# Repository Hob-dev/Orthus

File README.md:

# Orthus

An ergonomic split keyboard PCB with an integrated capacitive trackpad, Sharp Memory Display, and speaker. Designed around Kailh Choc low-profile switches and styled after Nothing.

## Overview

Orthus is a 6×5 ortholinear split — two mirrored halves, one with the alpha cluster (`QWERT`/`ASDFG`/`ZXCV`) and a number row (`1`–`5`), the other with the right-hand alphas, symbols, and a numpad row. Each half carries:

- 30 Kailh Choc keys (5 columns × 5 rows of alpha + outer modifier column + bottom-row arrow/macro circles)
- An integrated **OrthusTrackpad** capacitive sensor zone
- A **Sharp Memory Display** for live status (signal, battery, WPM, layer)
- Two side encoders / buttons next to the display
- A speaker grille

Both halves side-by-side:

Top-down view:

## Status

**Functionally complete** — finishing touches remain before fabrication (see "Known gaps" below).

## Folder layout

```
Orthus/
├── KiCad/              Main KiCad 7+ project — open Orthus.kicad_pro
│   ├── Orthus.kicad_pcb        Main board layout
│   ├── Orthus.kicad_sch        Top-level schematic (loads sub-sheets)
│   ├── Left.kicad_sch          Left-half hierarchical sheet
│   ├── Right.kicad_sch         Right-half hierarchical sheet
│   ├── LeftMatrix.kicad_sch    Switch matrix sub-sheet
│   ├── OLED.kicad_sch          Display sub-sheet
│   ├── led.kicad_sch / led_r.kicad_sch   LED sub-sheets
│   ├── font/                   Custom silkscreen font SVGs (digits 0–9)
│   └── backups/                Dated KiCad auto-backups
├── Renders/            Project renders, layout studies, and WIP photos
├── 3D/                 Mechanical models — case, keycaps, trackpad
│   ├── Orthus.step / .stl / .gltf / .bin     Full assembly
│   ├── OrthusSimple*.step                    Simplified assembly variants
│   ├── OrthusKeycap*.step                    Keycap variants (Alt, TLBR, TRBL)
│   ├── AltarCap v2/v3.step                   Sculpted altar-style keycaps
│   ├── OrthusTrackpad*.step                  Trackpad PCB models
│   └── TM040YDHG32.step                      LCD reference model
├── Fabrication/        Trackpad grill cutouts (.dxf / .svg, square + slotted)
├── JLCPCB/             Empty — gerbers for the main PCB not yet generated
└── Components/
    ├── OrthusTrackpad/    Capacitive trackpad PCB (self-contained KiCad project + gerbers)
    └── OrthusSharp/       Sharp Memory Display breakout (KiCad project + gerbers)
```

## Components

| Component | Purpose | Status |
|---|---|---|
| **OrthusTrackpad** | Custom mutual-capacitance trackpad PCB integrated into each half. Self-contained KiCad project with its own JLCPCB gerber output. | Complete |
| **OrthusSharp** | Sharp Memory Display breakout, derived from an open-source `sharp_memory_display` design and significantly modified. KiCad 5 originals preserved under `Components/OrthusSharp/Legacy/`. | Complete |
| **OrthusMouseWheel** | Scroll wheel module — *not included in this repo, still under `Custom/Ergomania/OrthusMouseWheel/`.* | Unfinished |

## Alternative Renders

| | |
|---|---|
|  |  |
|  |  |
|  |  |
|  |  |

Layout studies and design exploration:

## Known gaps

- **No gerbers / JLCPCB order files** for the main Orthus PCB. `JLCPCB/` is an empty placeholder — gerbers need to be generated before fabrication.
- **No BOM / pick-and-place files** for the main PCB.
- **No assembly documentation** — refer to the hierarchical schematics under `KiCad/`.
- **3D model paths in `Orthus.kicad_pcb`** still reference absolute paths under `E:/EverythingKB/Custom/Ergomania/OrthusChoc/...`. The 3D viewer works locally because of this; for an open-source release these should be repointed at `Orthus/3D/`.
- **3D model path in `OrthusSharp.kicad_pro`** uses `../../Custom/Ergomania/test/OrthusSharp.step` (relative to its old location).
- **OrthusSharp `fp-lib-table`** carries hardcoded macOS paths (`/Users/karnadi/...`) inherited from the upstream fork — regenerate or repoint to your local KiCad libraries on first open.

## Attribution

`Components/OrthusSharp/` is derived from an open-source Sharp Memory Display breakout (see `Components/OrthusSharp/LICENSE`). Heavily modified for integration with Orthus.

## License

Orthus is licensed under the [Creative Commons Attribution-NonCommercial 4.0 International License (CC BY-NC 4.0)](https://creativecommons.org/licenses/by-nc/4.0/).

`Components/OrthusSharp/` is third-party and retains its original license — see [`Components/OrthusSharp/LICENSE`](Components/OrthusSharp/LICENSE).

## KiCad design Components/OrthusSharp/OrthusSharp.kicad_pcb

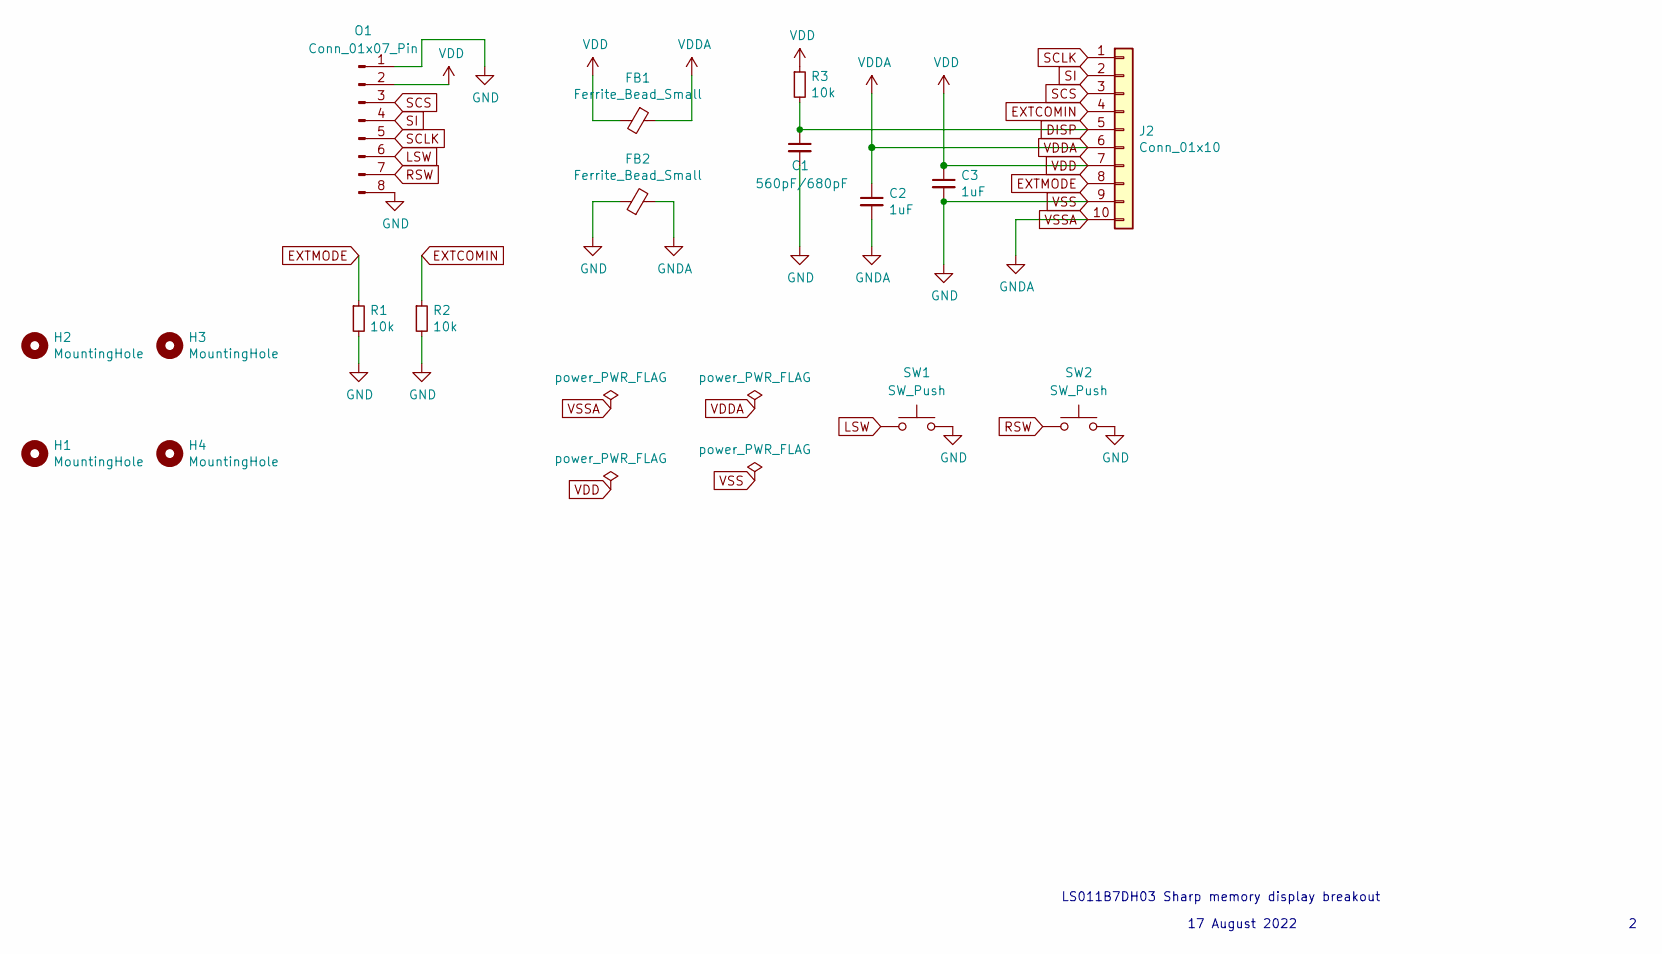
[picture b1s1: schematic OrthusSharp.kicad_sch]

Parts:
C1: 560pF/680pF; C_0603_1608Metric_Pad1.08x0.95mm_HandSolder; LCSC C84721
C2, C3: 1uF; C_0603_1608Metric_Pad1.08x0.95mm_HandSolder; LCSC C15849
FB1, FB2: Ferrite_Bead_Small; R_0805_2012Metric_Pad1.20x1.40mm_HandSolder; LCSC C1017
H1, H2, H3, H4: MountingHole; SMD-1_SMTSO1620MTJ
J2: Conn_01x10; FPC-SMD_10P-P0.50_XUNPU_FPC-05F-10PH15; LCSC C506791
O1: Conn_01x07_Pin; FPC-SMD_8P-P0.50_XUNPU_FPC-05F-8PH15
R1, R2, R3: 10k; R_0603_1608Metric_Pad0.98x0.95mm_HandSolder; LCSC C25804
SW1, SW2: SW_Push; SW-SMD_4P-L5.1-W5.1-P3.70-LS6.5-TL_H3.5

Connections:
DISP: C1.1, J2.5, R3.2
EXTCOMIN: J2.4, R2.1
EXTMODE: J2.8, R1.1
LSW: O1.6, SW1.1
RSW: O1.7, SW2.1
SCLK: J2.1, O1.5
SCS: J2.3, O1.3
SI: J2.2, O1.4
VDD: C3.1, FB1.2, J2.7, O1.2, R3.1
VDDA: C2.1, FB1.1, J2.6
VSS: C1.2, C3.2, FB2.1, J2.9, O1.1, O1.8, R1.2, R2.2, SW1.2, SW2.2
VSSA: C2.2, FB2.2, J2.10

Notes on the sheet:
17 August 2022
LS011B7DH03 Sharp memory display breakout

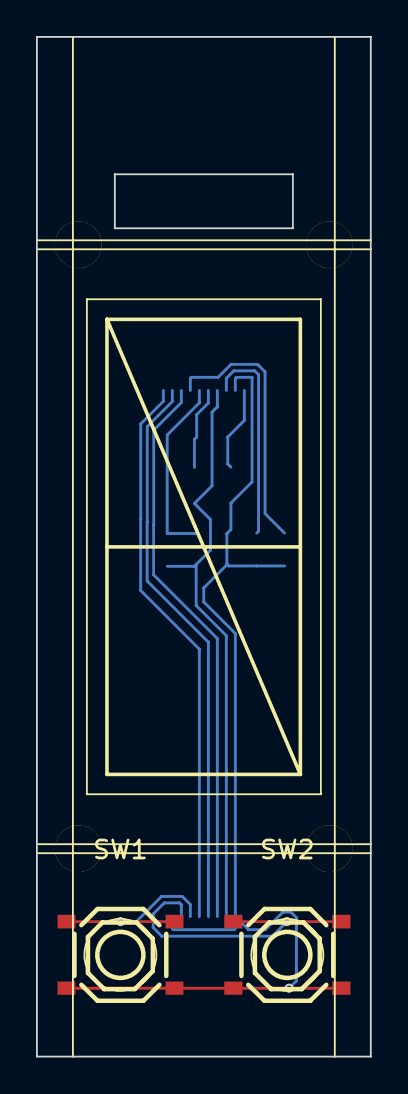
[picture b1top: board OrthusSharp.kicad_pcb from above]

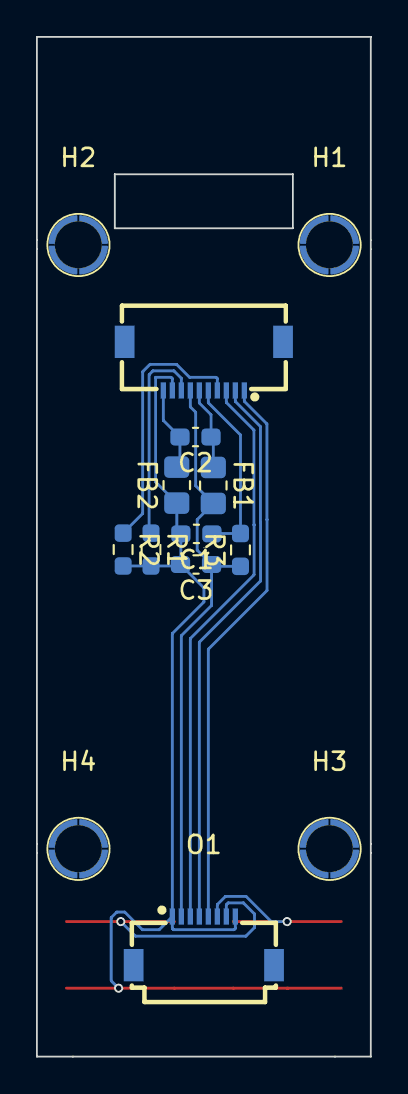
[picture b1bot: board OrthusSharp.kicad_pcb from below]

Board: 2 copper layers, 18.6 x 56.6 mm, 16 parts (14 on the bottom side), 12 nets.

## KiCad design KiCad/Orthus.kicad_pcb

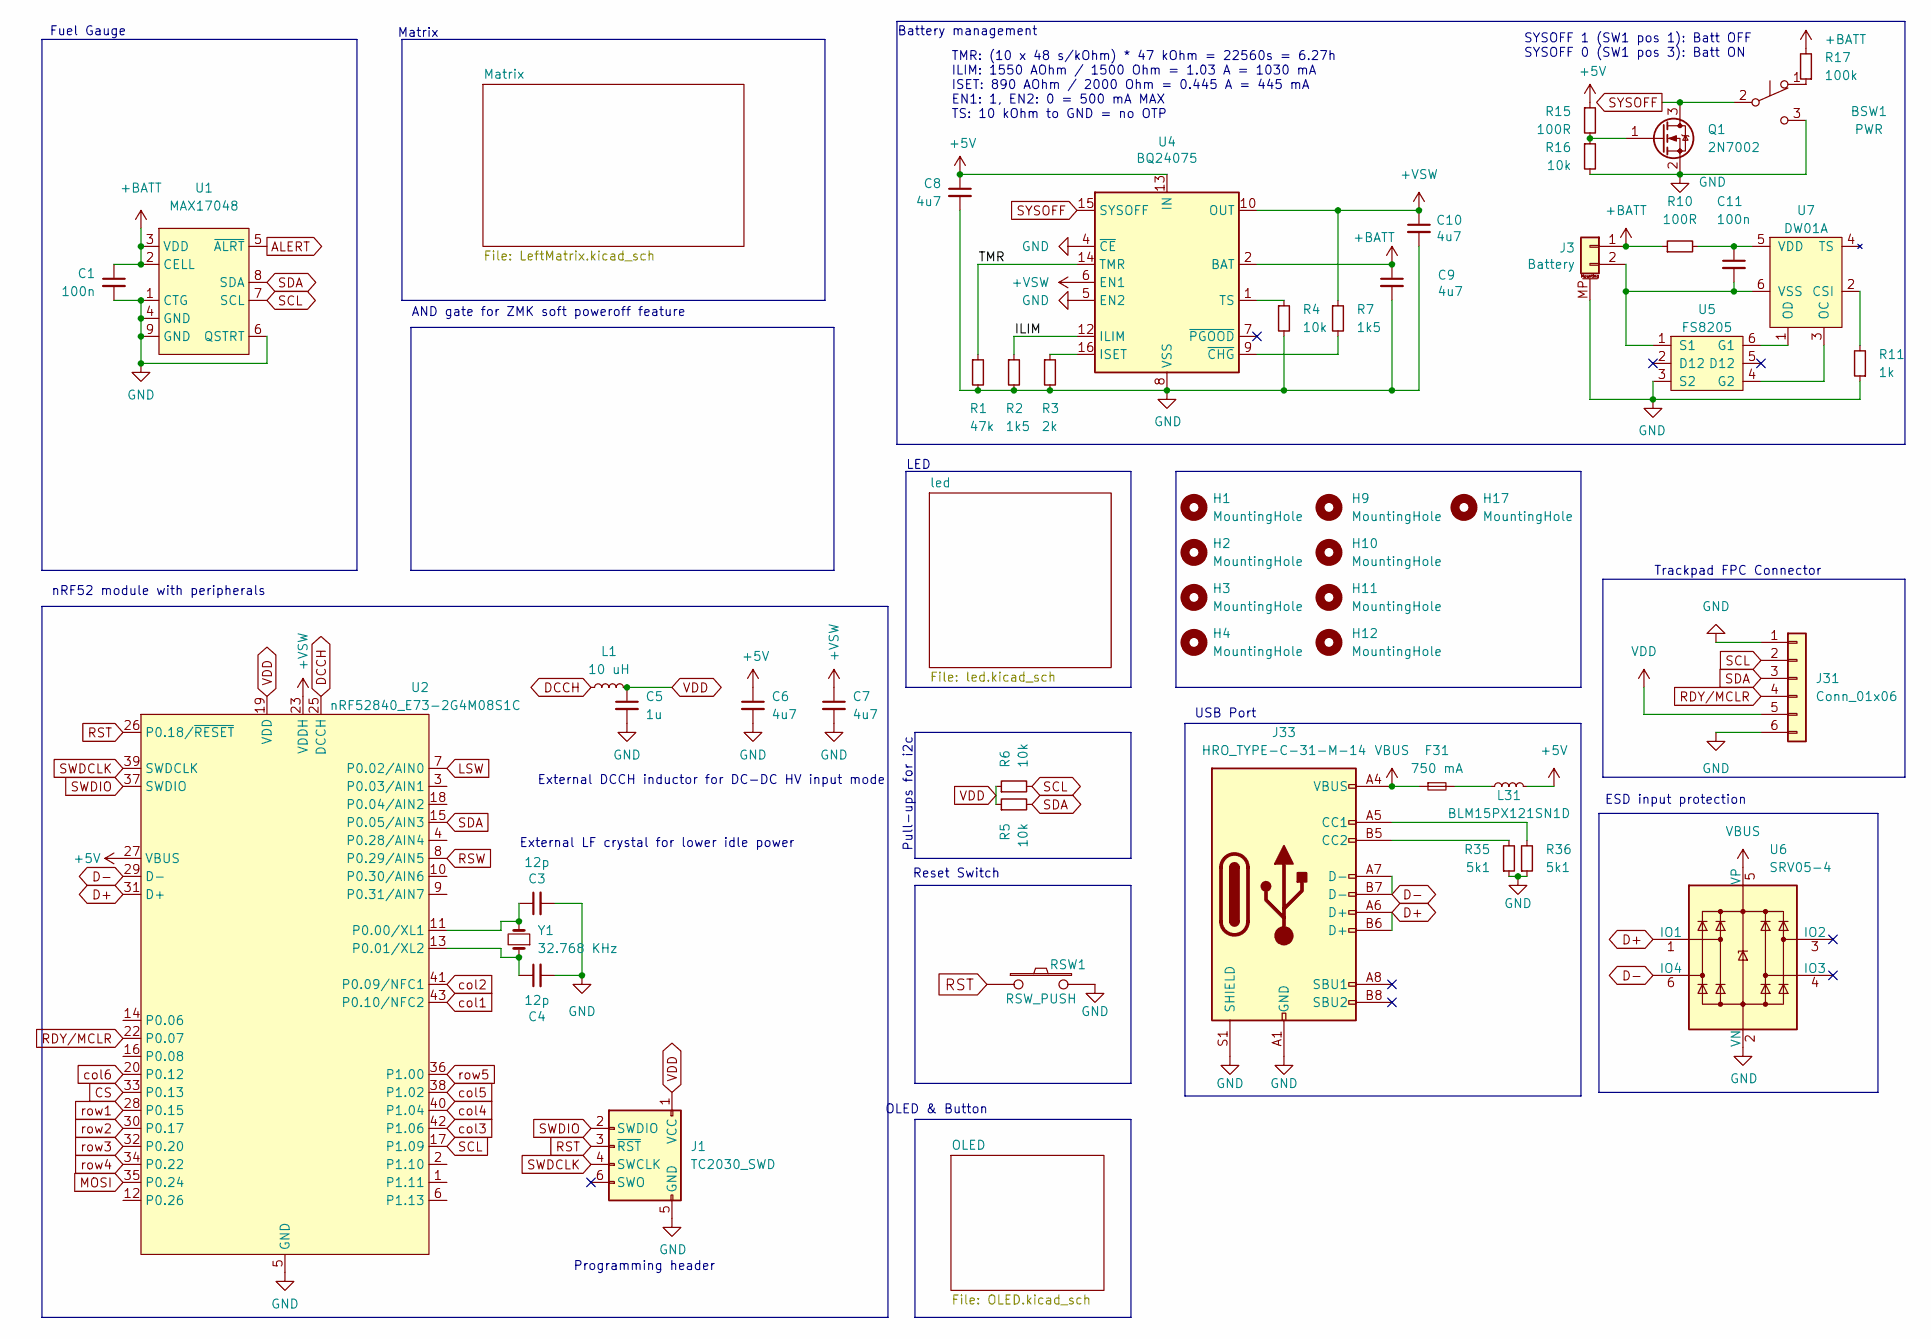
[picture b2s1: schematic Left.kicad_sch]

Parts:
BSW1: PWR; SW_MSK12C02-HB
C1: 100n; C_0402_1005Metric; LCSC C307331
C3, C4: 12p; C_0402_1005Metric; LCSC C1547
C5: 1u; C_0402_1005Metric; LCSC C52923
C6, C7: 4u7; C_0402_1005Metric; LCSC C23733
C8, C9, C10: 4u7; C_0402_1005Metric
C11: 100n; C_0402_1005Metric
F31: 750 mA; Fuse_0603_1608Metric
H1, H2, H3, H4: MountingHole; SMD-1_SMTSO1620MTJ
H9, H10, H11, H12, H17: MountingHole; SMD_BD5.6-L5.6-W5.6-D3.6
J1: TC2030_SWD; CON_TC2030_outlined
J3: Battery; Molex_Pico-EZmate_78171-0002_1x02-1MP_P1.20mm_Vertical; LCSC C505023
J31: Conn_01x06; FPC-SMD_6P-P0.50_XUNPU_FPC-05F-6PH15
J33: HRO_TYPE-C-31-M-14; USB_C_Receptacle_HRO_TYPE-C-31-M-14
L1: 10 uH; L_0603_1608Metric; LCSC C92982
L31: BLM15PX121SN1D; L_0402_1005Metric
Q1: 2N7002; SOT-23
R1: 47k; R_0402_1005Metric
R2, R7: 1k5; R_0402_1005Metric
R3: 2k; R_0402_1005Metric
R4, R16: 10k; R_0402_1005Metric
R5, R6: 10k; R_0402_1005Metric; LCSC C25744
R10, R15: 100R; R_0402_1005Metric
R11: 1k; R_0402_1005Metric
R17: 100k; R_0402_1005Metric
R35, R36: 5k1; R_0402_1005Metric
RSW1: RSW_PUSH; SW-SMD_4P-L5.1-W5.1-P3.70-LS6.5-TL_H1.5
U1: MAX17048; DFN-8-1EP_2x2mm_P0.5mm_EP0.6x1.2mm; LCSC C2682616
U2: nRF52840_E73-2G4M08S1C; LCSC C356849
U4: BQ24075; VQFN-16-1EP_3x3mm_P0.5mm_EP1.6x1.6mm
U5: FS8205; SOT-23-6; LCSC C32254
U6: SRV05-4; SOT-23-6-routable; LCSC C7420376
U7: DW01A; SOT-23-6; LCSC C61503
Y1: 32.768 KHz; Crystal_SMD_2012-2Pin_2.0x1.2mm; LCSC C55208

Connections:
+5V: C6.1, C8.1, L31.2, R15.1, U2.27 (VBUS), U4.13 (IN)
+BATT: C1.1, C9.1, J3.1, R10.1, R17.2, U1.2 (CELL), U1.3 (VDD), U4.2 (BAT), U4.3 (BAT)
+VSW: C7.1, C10.1, R7.1, U2.23 (VDDH), U4.6 (EN1), U4.10 (OUT), U4.11 (OUT); also elsewhere on the board
/Left/ILIM: R2.1, U4.12 (ILIM)
/Left/TMR: R1.1, U4.14 (TMR)
ALERT: U1.5 (~ALRT)
CS: U2.33 (P0.13); also elsewhere on the board
D+: J33.A6 (D+), J33.B6 (D+), U2.31 (D+), U6.1 (IO1)
D-: J33.A7 (D-), J33.B7 (D-), U2.29 (D-), U6.6 (IO4)
DCCH: L1.1, U2.25 (DCCH)
GND: BSW1.3 (C), C1.2, C3.2, C4.2, C5.2, C6.2, C7.2, C8.2, C9.2, C10.2, J1.5 (GND), J3.MP (MountPin), J31.1, J31.6, J33.A1 (GND), J33.A12 (GND), J33.B1 (GND), J33.B12 (GND), J33.S1 (SHIELD), Q1.2 (S), R1.2, R2.2, R3.2, R4.2, R11.1, R16.2, R35.1, R36.1, RSW1.2, U1.1 (CTG), U1.4 (GND), U1.6 (QSTRT), U1.9 (GND), U2.5 (GND), U2.21 (GND), U2.24 (GND), U4.4 (~CE), U4.5 (EN2), U4.8 (VSS), U4.17 (VSS), U5.3 (S2), U6.2 (VN); also elsewhere on the board
LSW: U2.7 (P0.02/AIN0); also elsewhere on the board
MOSI: U2.35 (P0.24); also elsewhere on the board
unnamed: BSW1.1 (A), R17.1
unnamed: F31.2, L31.1
unnamed: C11.2, J3.2, U5.1 (S1), U7.6 (VSS)
unnamed: J33.A5 (CC1), R36.2
unnamed: J33.B5 (CC2), R35.2
unnamed: Q1.1 (G), R15.2, R16.1
unnamed: C3.1, U2.11 (P0.00/XL1), Y1.2
unnamed: C4.1, U2.13 (P0.01/XL2), Y1.1
unnamed: R3.1, U4.16 (ISET)
unnamed: R4.1, U4.1 (TS)
unnamed: R7.2, U4.9 (~CHG)
unnamed: U5.6 (G1), U7.1 (OD)
unnamed: U5.4 (G2), U7.3 (OC)
unnamed: R11.2, U7.2 (CSI)
unnamed: C11.1, R10.2, U7.5 (VDD)
RDY/MCLR: J31.4, U2.22 (P0.07)
RST: J1.3 (~RST), RSW1.1, U2.26 (P0.18/~RESET)
RSW: U2.8 (P0.29/AIN5); also elsewhere on the board
SCL: J31.2, R6.2, U1.7 (SCL), U2.17 (P1.09); also elsewhere on the board
SDA: J31.3, R5.2, U1.8 (SDA), U2.15 (P0.05/AIN3)
SWDCLK: J1.4 (SWCLK), U2.39 (SWDCLK)
SWDIO: J1.2 (SWDIO), U2.37 (SWDIO)
SYSOFF: BSW1.2 (B), Q1.3 (D), U4.15 (SYSOFF)
VBUS: F31.1, J33.A4 (VBUS), J33.A9 (VBUS), J33.B4 (VBUS), J33.B9 (VBUS), U6.5 (VP)
VDD: C5.1, J1.1 (VCC), J31.5, L1.2, R5.1, R6.1, U2.19 (VDD); also elsewhere on the board
col1: U2.43 (P0.10/NFC2); also elsewhere on the board
col2: U2.41 (P0.09/NFC1); also elsewhere on the board
col3: U2.42 (P1.06); also elsewhere on the board
col4: U2.40 (P1.04); also elsewhere on the board
col5: U2.38 (P1.02); also elsewhere on the board
col6: U2.20 (P0.12); also elsewhere on the board
row2: U2.30 (P0.17); also elsewhere on the board
row3: U2.32 (P0.20); also elsewhere on the board
row4: U2.34 (P0.22); also elsewhere on the board
row5: U2.36 (P1.00); also elsewhere on the board

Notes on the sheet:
SYSOFF 1 (SW1 pos 1): Batt OFF SYSOFF 0 (SW1 pos 3): Batt ON
nRF52 module with peripherals
External DCCH inductor for DC-DC HV input mode
Trackpad FPC Connector
Programming header
Reset Switch
Pull-ups for i2c
Battery management
Matrix
OLED & Button
ESD input protection
TMR: (10 x 48 s/kOhm) * 47 kOhm = 22560s = 6.27h ILIM: 1550 AOhm / 1500 Ohm = 1.03 A = 1030 mA ISET: 890 AOhm / 2000 Ohm = 0.445 A = 445 mA EN1: 1, EN2: 0 = 500 mA MAX TS: 10 kOhm to GND = no OTP
USB Port
AND gate for ZMK soft poweroff feature
LED
Fuel Gauge
External LF crystal for lower idle power

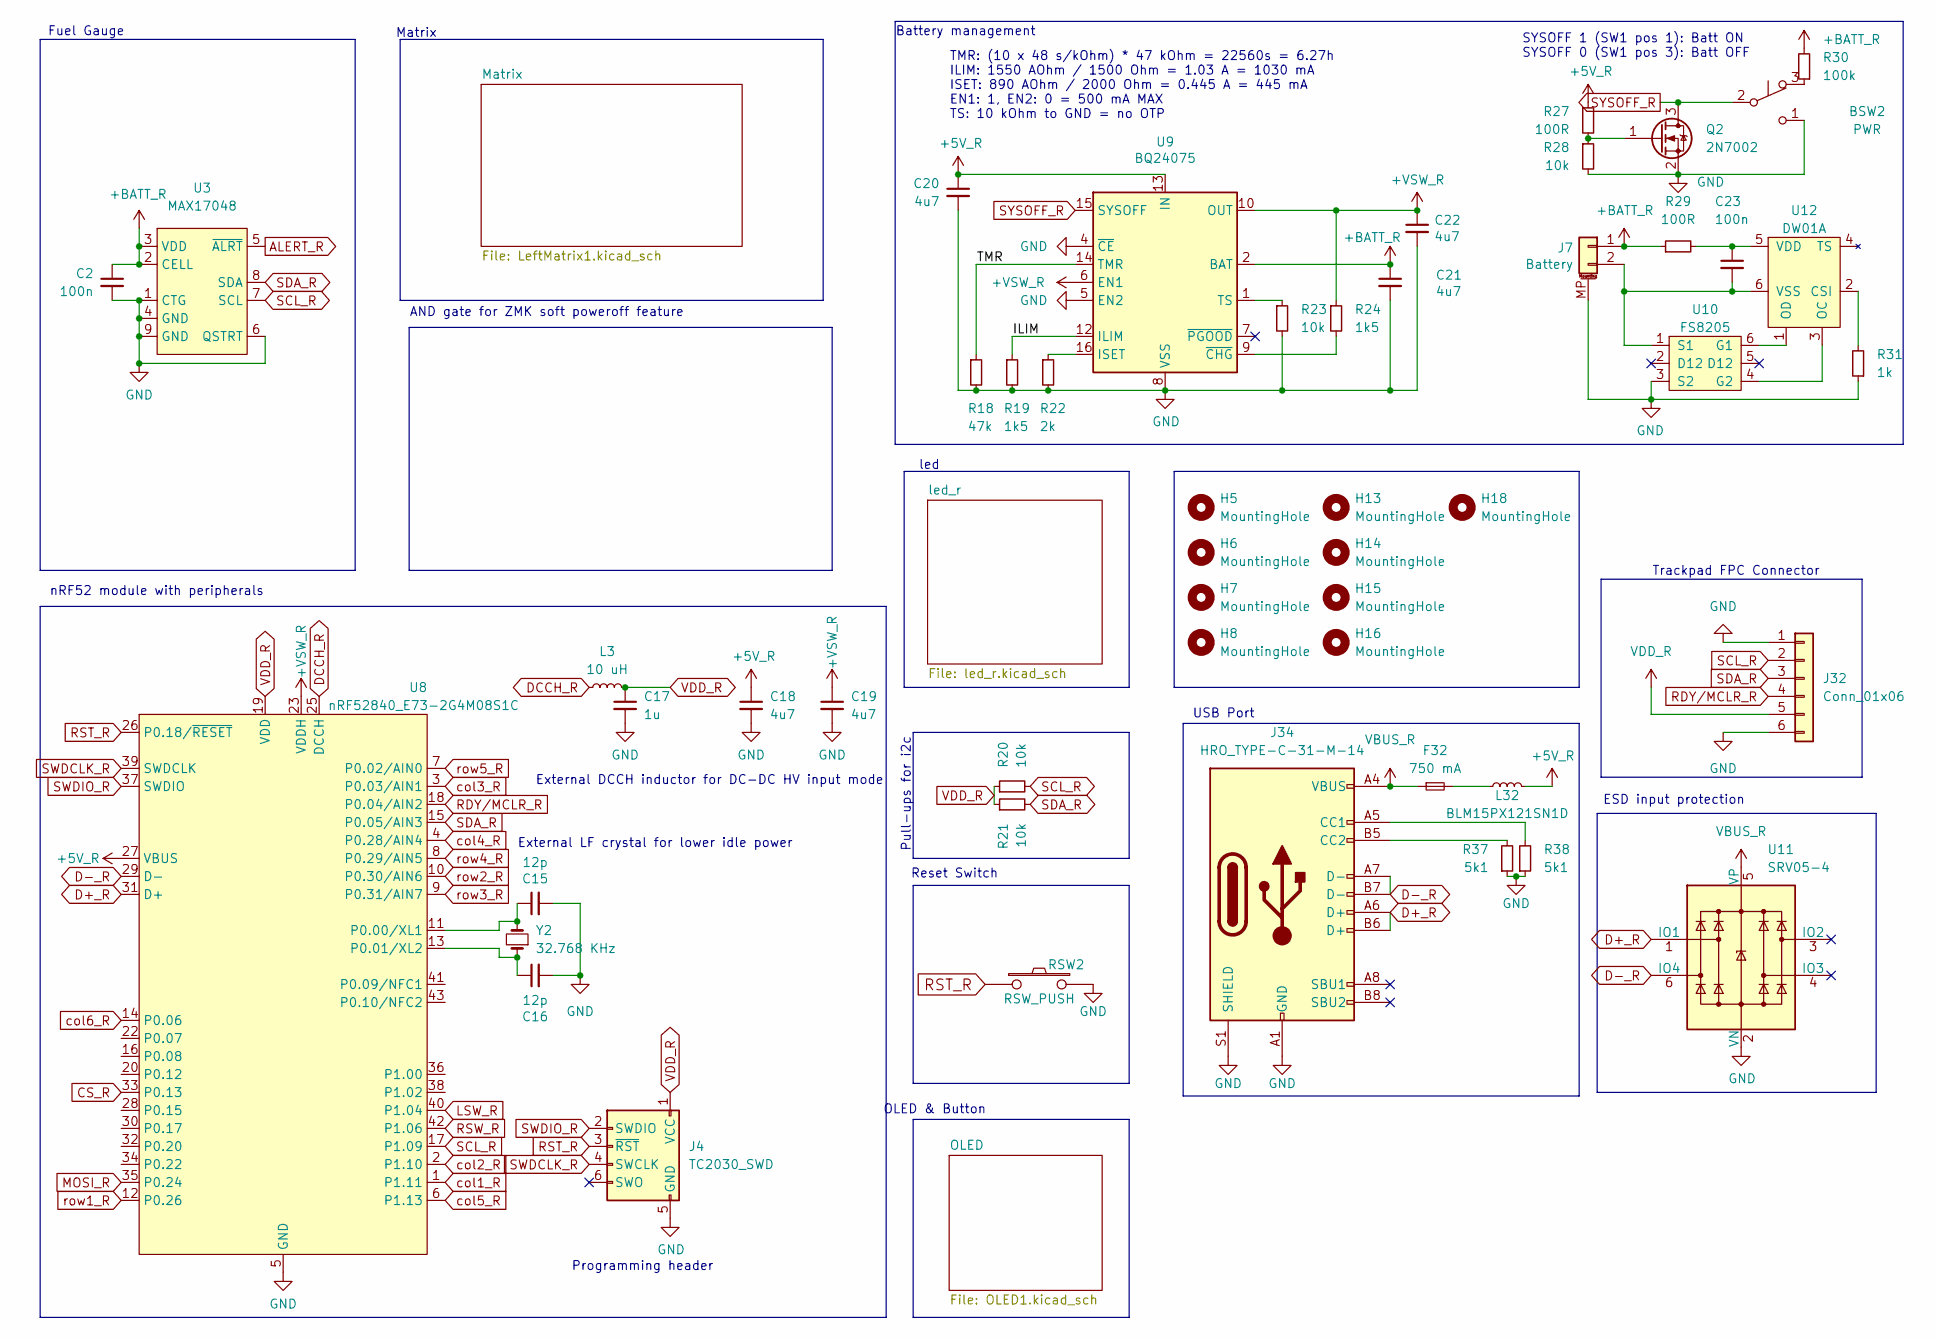
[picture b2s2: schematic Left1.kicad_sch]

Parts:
BSW2: PWR; SW_MSK12C02-HB
C2: 100n; C_0402_1005Metric; LCSC C307331
C15, C16: 12p; C_0402_1005Metric; LCSC C1547
C17: 1u; C_0402_1005Metric; LCSC C52923
C18, C19: 4u7; C_0402_1005Metric; LCSC C23733
C20, C21, C22: 4u7; C_0402_1005Metric
C23: 100n; C_0402_1005Metric
F32: 750 mA; Fuse_0603_1608Metric
H5, H6, H7, H8: MountingHole; SMD-1_SMTSO1620MTJ
H13, H14, H15, H16, H18: MountingHole; SMD_BD5.6-L5.6-W5.6-D3.6
J4: TC2030_SWD; CON_TC2030_outlined
J7: Battery; Molex_Pico-EZmate_78171-0002_1x02-1MP_P1.20mm_Vertical; LCSC C505023
J32: Conn_01x06; FPC-SMD_6P-P0.50_XUNPU_FPC-05F-6PH15
J34: HRO_TYPE-C-31-M-14; USB_C_Receptacle_HRO_TYPE-C-31-M-14
L3: 10 uH; L_0603_1608Metric; LCSC C92982
L32: BLM15PX121SN1D; L_0402_1005Metric
Q2: 2N7002; SOT-23
R18: 47k; R_0402_1005Metric
R19, R24: 1k5; R_0402_1005Metric
R20, R21: 10k; R_0402_1005Metric; LCSC C25744
R22: 2k; R_0402_1005Metric
R23, R28: 10k; R_0402_1005Metric
R27, R29: 100R; R_0402_1005Metric
R30: 100k; R_0402_1005Metric
R31: 1k; R_0402_1005Metric
R37, R38: 5k1; R_0402_1005Metric
RSW2: RSW_PUSH; SW-SMD_4P-L5.1-W5.1-P3.70-LS6.5-TL_H1.5
U3: MAX17048; DFN-8-1EP_2x2mm_P0.5mm_EP0.6x1.2mm; LCSC C2682616
U8: nRF52840_E73-2G4M08S1C; LCSC C356849
U9: BQ24075; VQFN-16-1EP_3x3mm_P0.5mm_EP1.6x1.6mm
U10: FS8205; SOT-23-6; LCSC C32254
U11: SRV05-4; SOT-23-6-routable; LCSC C7420376
U12: DW01A; SOT-23-6; LCSC C61503
Y2: 32.768 KHz; Crystal_SMD_2012-2Pin_2.0x1.2mm; LCSC C55208

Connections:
+5V_R: C18.1, C20.1, L32.2, R27.1, U8.27 (VBUS), U9.13 (IN)
+BATT_R: C2.1, C21.1, J7.1, R29.1, R30.2, U3.2 (CELL), U3.3 (VDD), U9.2 (BAT), U9.3 (BAT)
+VSW_R: C19.1, C22.1, R24.1, U8.23 (VDDH), U9.6 (EN1), U9.10 (OUT), U9.11 (OUT)
/Left1/ILIM: R19.1, U9.12 (ILIM)
/Left1/TMR: R18.1, U9.14 (TMR)
ALERT_R: U3.5 (~ALRT)
CS_R: U8.33 (P0.13); also elsewhere on the board
D+_R: J34.A6 (D+), J34.B6 (D+), U8.31 (D+), U11.1 (IO1)
D-_R: J34.A7 (D-), J34.B7 (D-), U8.29 (D-), U11.6 (IO4)
DCCH_R: L3.1, U8.25 (DCCH)
GND: BSW2.1 (C), C2.2, C15.2, C16.2, C17.2, C18.2, C19.2, C20.2, C21.2, C22.2, J4.5 (GND), J7.MP (MountPin), J32.1, J32.6, J34.A1 (GND), J34.A12 (GND), J34.B1 (GND), J34.B12 (GND), J34.S1 (SHIELD), Q2.2 (S), R18.2, R19.2, R22.2, R23.2, R28.2, R31.1, R37.1, R38.1, RSW2.2, U3.1 (CTG), U3.4 (GND), U3.6 (QSTRT), U3.9 (GND), U8.5 (GND), U8.21 (GND), U8.24 (GND), U9.4 (~CE), U9.5 (EN2), U9.8 (VSS), U9.17 (VSS), U10.3 (S2), U11.2 (VN); also elsewhere on the board
LSW_R: U8.40 (P1.04); also elsewhere on the board
MOSI_R: U8.35 (P0.24); also elsewhere on the board
unnamed: BSW2.3 (A), R30.1
unnamed: F32.2, L32.1
unnamed: C23.2, J7.2, U10.1 (S1), U12.6 (VSS)
unnamed: J34.A5 (CC1), R38.2
unnamed: J34.B5 (CC2), R37.2
unnamed: Q2.1 (G), R27.2, R28.1
unnamed: C15.1, U8.11 (P0.00/XL1), Y2.2
unnamed: C16.1, U8.13 (P0.01/XL2), Y2.1
unnamed: R22.1, U9.16 (ISET)
unnamed: R23.1, U9.1 (TS)
unnamed: R24.2, U9.9 (~CHG)
unnamed: U10.6 (G1), U12.1 (OD)
unnamed: U10.4 (G2), U12.3 (OC)
unnamed: R31.2, U12.2 (CSI)
unnamed: C23.1, R29.2, U12.5 (VDD)
RDY/MCLR_R: J32.4, U8.18 (P0.04/AIN2)
RST_R: J4.3 (~RST), RSW2.1, U8.26 (P0.18/~RESET)
RSW_R: U8.42 (P1.06); also elsewhere on the board
SCL_R: J32.2, R20.2, U3.7 (SCL), U8.17 (P1.09); also elsewhere on the board
SDA_R: J32.3, R21.2, U3.8 (SDA), U8.15 (P0.05/AIN3)
SWDCLK_R: J4.4 (SWCLK), U8.39 (SWDCLK)
SWDIO_R: J4.2 (SWDIO), U8.37 (SWDIO)
SYSOFF_R: BSW2.2 (B), Q2.3 (D), U9.15 (SYSOFF)
VBUS_R: F32.1, J34.A4 (VBUS), J34.A9 (VBUS), J34.B4 (VBUS), J34.B9 (VBUS), U11.5 (VP)
VDD_R: C17.1, J4.1 (VCC), J32.5, L3.2, R20.1, R21.1, U8.19 (VDD); also elsewhere on the board
col1_R: U8.1 (P1.11); also elsewhere on the board
col2_R: U8.2 (P1.10); also elsewhere on the board
col3_R: U8.3 (P0.03/AIN1); also elsewhere on the board
col4_R: U8.4 (P0.28/AIN4); also elsewhere on the board
col5_R: U8.6 (P1.13); also elsewhere on the board
col6_R: U8.14 (P0.06); also elsewhere on the board
row2_R: U8.10 (P0.30/AIN6); also elsewhere on the board
row3_R: U8.9 (P0.31/AIN7); also elsewhere on the board
row4_R: U8.8 (P0.29/AIN5); also elsewhere on the board
row5_R: U8.7 (P0.02/AIN0); also elsewhere on the board

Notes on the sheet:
SYSOFF 1 (SW1 pos 1): Batt ON SYSOFF 0 (SW1 pos 3): Batt OFF
nRF52 module with peripherals
External DCCH inductor for DC-DC HV input mode
Trackpad FPC Connector
Programming header
Reset Switch
Pull-ups for i2c
Battery management
Matrix
OLED & Button
ESD input protection
led
TMR: (10 x 48 s/kOhm) * 47 kOhm = 22560s = 6.27h ILIM: 1550 AOhm / 1500 Ohm = 1.03 A = 1030 mA ISET: 890 AOhm / 2000 Ohm = 0.445 A = 445 mA EN1: 1, EN2: 0 = 500 mA MAX TS: 10 kOhm to GND = no OTP
USB Port
AND gate for ZMK soft poweroff feature
Fuel Gauge
External LF crystal for lower idle power

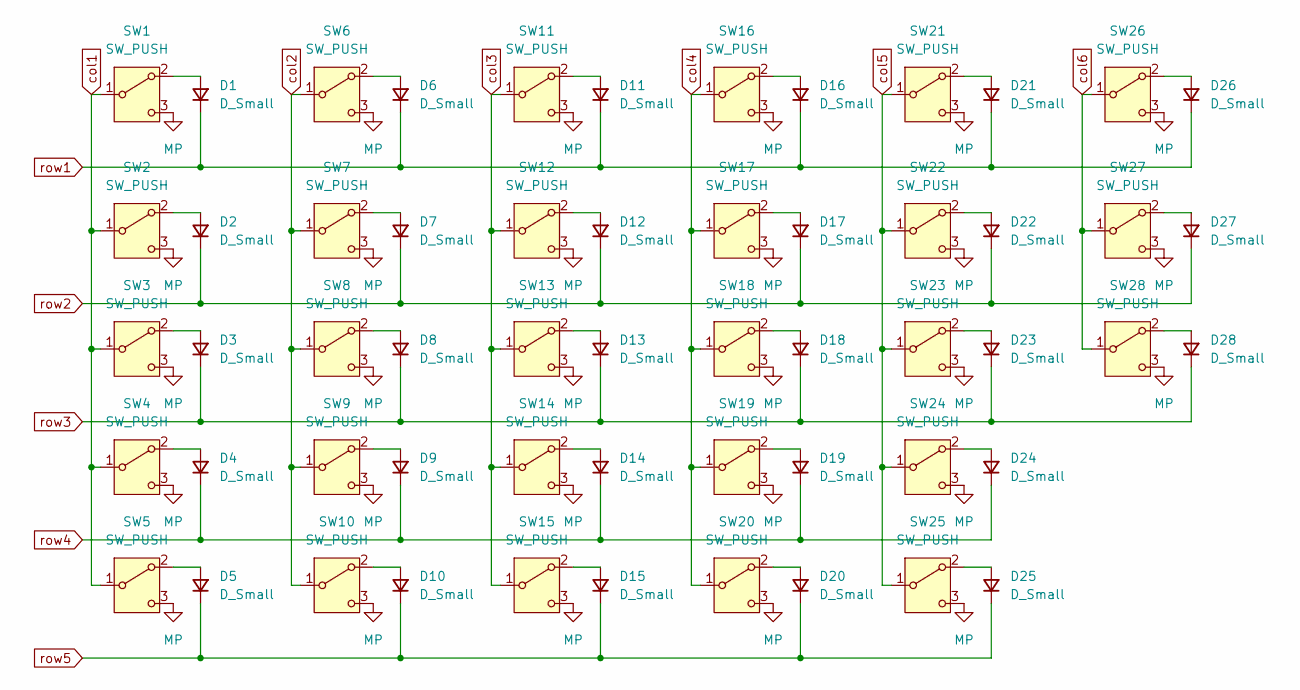
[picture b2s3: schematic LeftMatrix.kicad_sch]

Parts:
D1, D2, D3, D4, D5, D6, D7, D8, D9, D10, D11, D12, D13, D14, D15, D16, D17, D18, D19, D20, D21, D22, D23, D24, D25, D26, D27, D28: D_Small; D_SOD-123
SW1, SW2, SW3, SW4, SW5, SW6, SW7, SW8, SW9, SW10, SW11, SW12, SW13, SW14, SW15, SW16, SW17, SW18, SW19, SW20, SW21, SW22, SW23, SW24, SW25, SW26, SW27, SW28: SW_PUSH; HOB_CHOC_V1&V2

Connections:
unnamed: D2.2 (A), SW2.2 (A)
unnamed: D3.2 (A), SW3.2 (A)
unnamed: D4.2 (A), SW4.2 (A)
unnamed: D5.2 (A), SW5.2 (A)
unnamed: D6.2 (A), SW6.2 (A)
unnamed: D7.2 (A), SW7.2 (A)
unnamed: D8.2 (A), SW8.2 (A)
unnamed: D9.2 (A), SW9.2 (A)
unnamed: D10.2 (A), SW10.2 (A)
unnamed: D11.2 (A), SW11.2 (A)
unnamed: D12.2 (A), SW12.2 (A)
unnamed: D13.2 (A), SW13.2 (A)
unnamed: D14.2 (A), SW14.2 (A)
unnamed: D15.2 (A), SW15.2 (A)
unnamed: D16.2 (A), SW16.2 (A)
unnamed: D17.2 (A), SW17.2 (A)
unnamed: D18.2 (A), SW18.2 (A)
unnamed: D19.2 (A), SW19.2 (A)
unnamed: D20.2 (A), SW20.2 (A)
unnamed: D21.2 (A), SW21.2 (A)
unnamed: D22.2 (A), SW22.2 (A)
unnamed: D23.2 (A), SW23.2 (A)
unnamed: D24.2 (A), SW24.2 (A)
unnamed: D25.2 (A), SW25.2 (A)
unnamed: D26.2 (A), SW26.2 (A)
unnamed: D27.2 (A), SW27.2 (A)
unnamed: D28.2 (A), SW28.2 (A)
col1: SW1.1 (B), SW2.1 (B), SW3.1 (B), SW4.1 (B), SW5.1 (B); also elsewhere on the board
col2: SW6.1 (B), SW7.1 (B), SW8.1 (B), SW9.1 (B), SW10.1 (B); also elsewhere on the board
col3: SW11.1 (B), SW12.1 (B), SW13.1 (B), SW14.1 (B), SW15.1 (B); also elsewhere on the board
col4: SW16.1 (B), SW17.1 (B), SW18.1 (B), SW19.1 (B), SW20.1 (B); also elsewhere on the board
col5: SW21.1 (B), SW22.1 (B), SW23.1 (B), SW24.1 (B), SW25.1 (B); also elsewhere on the board
col6: SW26.1 (B), SW27.1 (B), SW28.1 (B); also elsewhere on the board
row2: D2.1 (K), D7.1 (K), D12.1 (K), D17.1 (K), D22.1 (K), D27.1 (K); also elsewhere on the board
row3: D3.1 (K), D8.1 (K), D13.1 (K), D18.1 (K), D23.1 (K), D28.1 (K); also elsewhere on the board
row4: D4.1 (K), D9.1 (K), D14.1 (K), D19.1 (K), D24.1 (K); also elsewhere on the board
row5: D5.1 (K), D10.1 (K), D15.1 (K), D20.1 (K), D25.1 (K); also elsewhere on the board

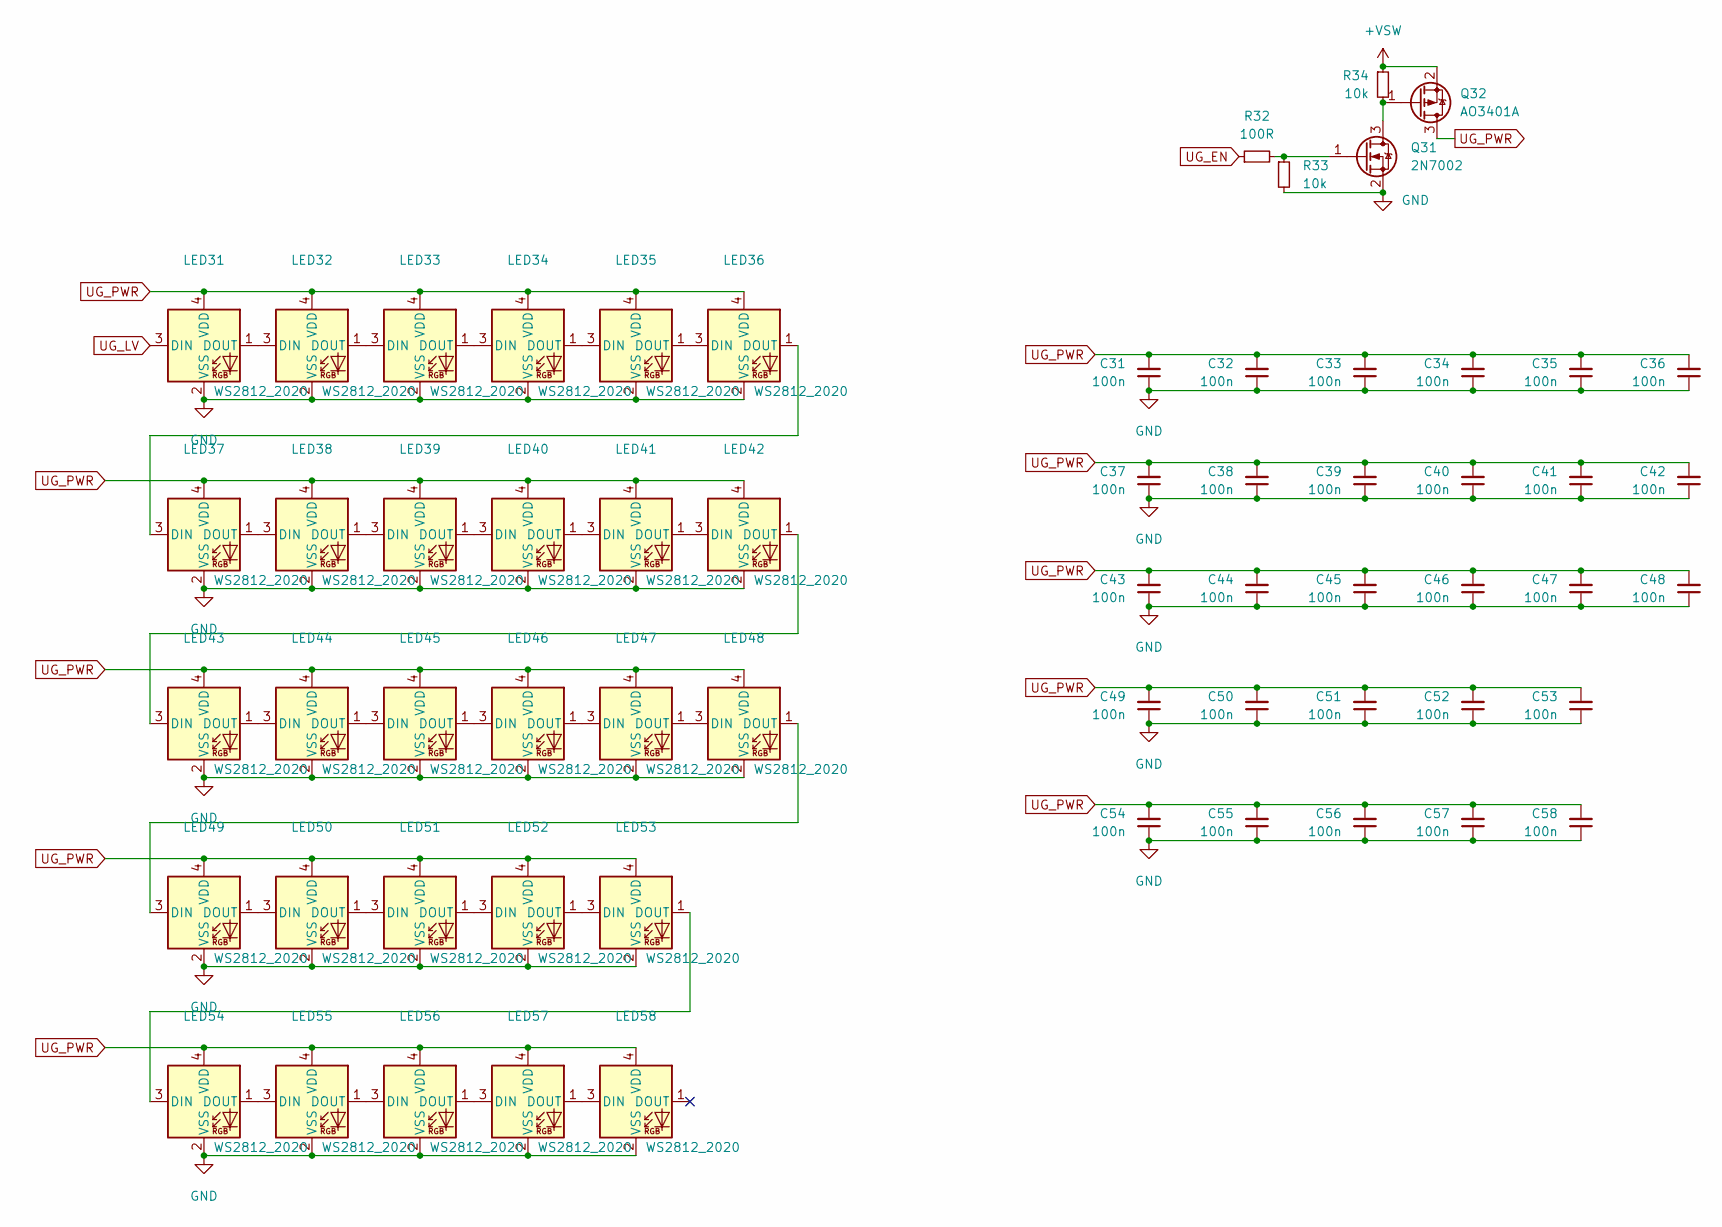
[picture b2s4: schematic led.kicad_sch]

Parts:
C31, C32, C33, C34, C35, C36, C37, C38, C39, C40, C41, C42, C43, C44, C45, C46, C47, C48, C49, C50, C51, C52, C53, C54, C55, C56, C57, C58: 100n; C_0402_1005Metric
LED31, LED32, LED33, LED34, LED35, LED36, LED37, LED38, LED39, LED40, LED41, LED42, LED43, LED44, LED45, LED46, LED47, LED48, LED49, LED50, LED51, LED52, LED53, LED54, LED55, LED56, LED57, LED58: WS2812_2020; YS-SK6812MINI-E
Q31: 2N7002; SOT-23
Q32: AO3401A; SOT-23
R32: 100R; R_0402_1005Metric
R33, R34: 10k; R_0402_1005Metric

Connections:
+VSW: Q32.2 (S), R34.1; also elsewhere on the board
GND: C31.1, C32.1, C33.1, C34.1, C35.1, C36.1, C37.1, C38.1, C39.1, C40.1, C41.1, C42.1, C43.1, C44.1, C45.1, C46.1, C47.1, C48.1, C49.1, C50.1, C51.1, C52.1, C53.1, C54.1, C55.1, C56.1, C57.1, C58.1, LED31.2 (VSS), LED32.2 (VSS), LED33.2 (VSS), LED34.2 (VSS), LED35.2 (VSS), LED36.2 (VSS), LED37.2 (VSS), LED38.2 (VSS), LED39.2 (VSS), LED40.2 (VSS), LED41.2 (VSS), LED42.2 (VSS), LED43.2 (VSS), LED44.2 (VSS), LED45.2 (VSS), LED46.2 (VSS), LED47.2 (VSS), LED48.2 (VSS), LED49.2 (VSS), LED50.2 (VSS), LED51.2 (VSS), LED52.2 (VSS), LED53.2 (VSS), LED54.2 (VSS), LED55.2 (VSS), LED56.2 (VSS), LED57.2 (VSS), LED58.2 (VSS), Q31.2 (S), R33.2; also elsewhere on the board
unnamed: LED31.1 (DOUT), LED32.3 (DIN)
unnamed: LED32.1 (DOUT), LED33.3 (DIN)
unnamed: LED33.1 (DOUT), LED34.3 (DIN)
unnamed: LED34.1 (DOUT), LED35.3 (DIN)
unnamed: LED35.1 (DOUT), LED36.3 (DIN)
unnamed: LED36.1 (DOUT), LED37.3 (DIN)
unnamed: LED37.1 (DOUT), LED38.3 (DIN)
unnamed: LED38.1 (DOUT), LED39.3 (DIN)
unnamed: LED39.1 (DOUT), LED40.3 (DIN)
unnamed: LED40.1 (DOUT), LED41.3 (DIN)
unnamed: LED41.1 (DOUT), LED42.3 (DIN)
unnamed: LED42.1 (DOUT), LED43.3 (DIN)
unnamed: LED43.1 (DOUT), LED44.3 (DIN)
unnamed: LED44.1 (DOUT), LED45.3 (DIN)
unnamed: LED45.1 (DOUT), LED46.3 (DIN)
unnamed: LED46.1 (DOUT), LED47.3 (DIN)
unnamed: LED47.1 (DOUT), LED48.3 (DIN)
unnamed: LED48.1 (DOUT), LED49.3 (DIN)
unnamed: LED49.1 (DOUT), LED50.3 (DIN)
unnamed: LED50.1 (DOUT), LED51.3 (DIN)
unnamed: LED51.1 (DOUT), LED52.3 (DIN)
unnamed: LED52.1 (DOUT), LED53.3 (DIN)
unnamed: LED53.1 (DOUT), LED54.3 (DIN)
unnamed: LED54.1 (DOUT), LED55.3 (DIN)
unnamed: LED55.1 (DOUT), LED56.3 (DIN)
unnamed: LED56.1 (DOUT), LED57.3 (DIN)
unnamed: LED57.1 (DOUT), LED58.3 (DIN)
unnamed: Q31.3 (D), Q32.1 (G), R34.2
unnamed: Q31.1 (G), R32.2, R33.1
UG_EN: R32.1
UG_LV: LED31.3 (DIN)
UG_PWR: C31.2, C32.2, C33.2, C34.2, C35.2, C36.2, C37.2, C38.2, C39.2, C40.2, C41.2, C42.2, C43.2, C44.2, C45.2, C46.2, C47.2, C48.2, C49.2, C50.2, C51.2, C52.2, C53.2, C54.2, C55.2, C56.2, C57.2, C58.2, LED31.4 (VDD), LED32.4 (VDD), LED33.4 (VDD), LED34.4 (VDD), LED35.4 (VDD), LED36.4 (VDD), LED37.4 (VDD), LED38.4 (VDD), LED39.4 (VDD), LED40.4 (VDD), LED41.4 (VDD), LED42.4 (VDD), LED43.4 (VDD), LED44.4 (VDD), LED45.4 (VDD), LED46.4 (VDD), LED47.4 (VDD), LED48.4 (VDD), LED49.4 (VDD), LED50.4 (VDD), LED51.4 (VDD), LED52.4 (VDD), LED53.4 (VDD), LED54.4 (VDD), LED55.4 (VDD), LED56.4 (VDD), LED57.4 (VDD), LED58.4 (VDD), Q32.3 (D)

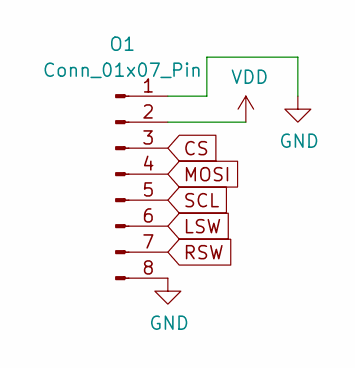
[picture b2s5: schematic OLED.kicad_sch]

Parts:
O1: Conn_01x07_Pin; FPC-SMD_8P-P0.50_XUNPU_FPC-05F-8PH15

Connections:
CS: O1.3; also elsewhere on the board
GND: O1.1, O1.8; also elsewhere on the board
LSW: O1.6; also elsewhere on the board
MOSI: O1.4; also elsewhere on the board
RSW: O1.7; also elsewhere on the board
SCL: O1.5; also elsewhere on the board
VDD: O1.2; also elsewhere on the board
